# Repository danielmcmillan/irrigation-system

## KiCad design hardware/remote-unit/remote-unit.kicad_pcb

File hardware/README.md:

## PCBs

PCBs are designed using KiCad.

"irrigation-controller" contains the KiCad project for the central control board.

"remote-unit" contains the KiCad project for the remote solenoid control board.

### Libraries

Some project-specific symbols and footprints are saved in the lib dir.

This external symbol and footprint is used with name "TPS54331DR": https://octopart.com/tps54331dr-texas+instruments-12190905

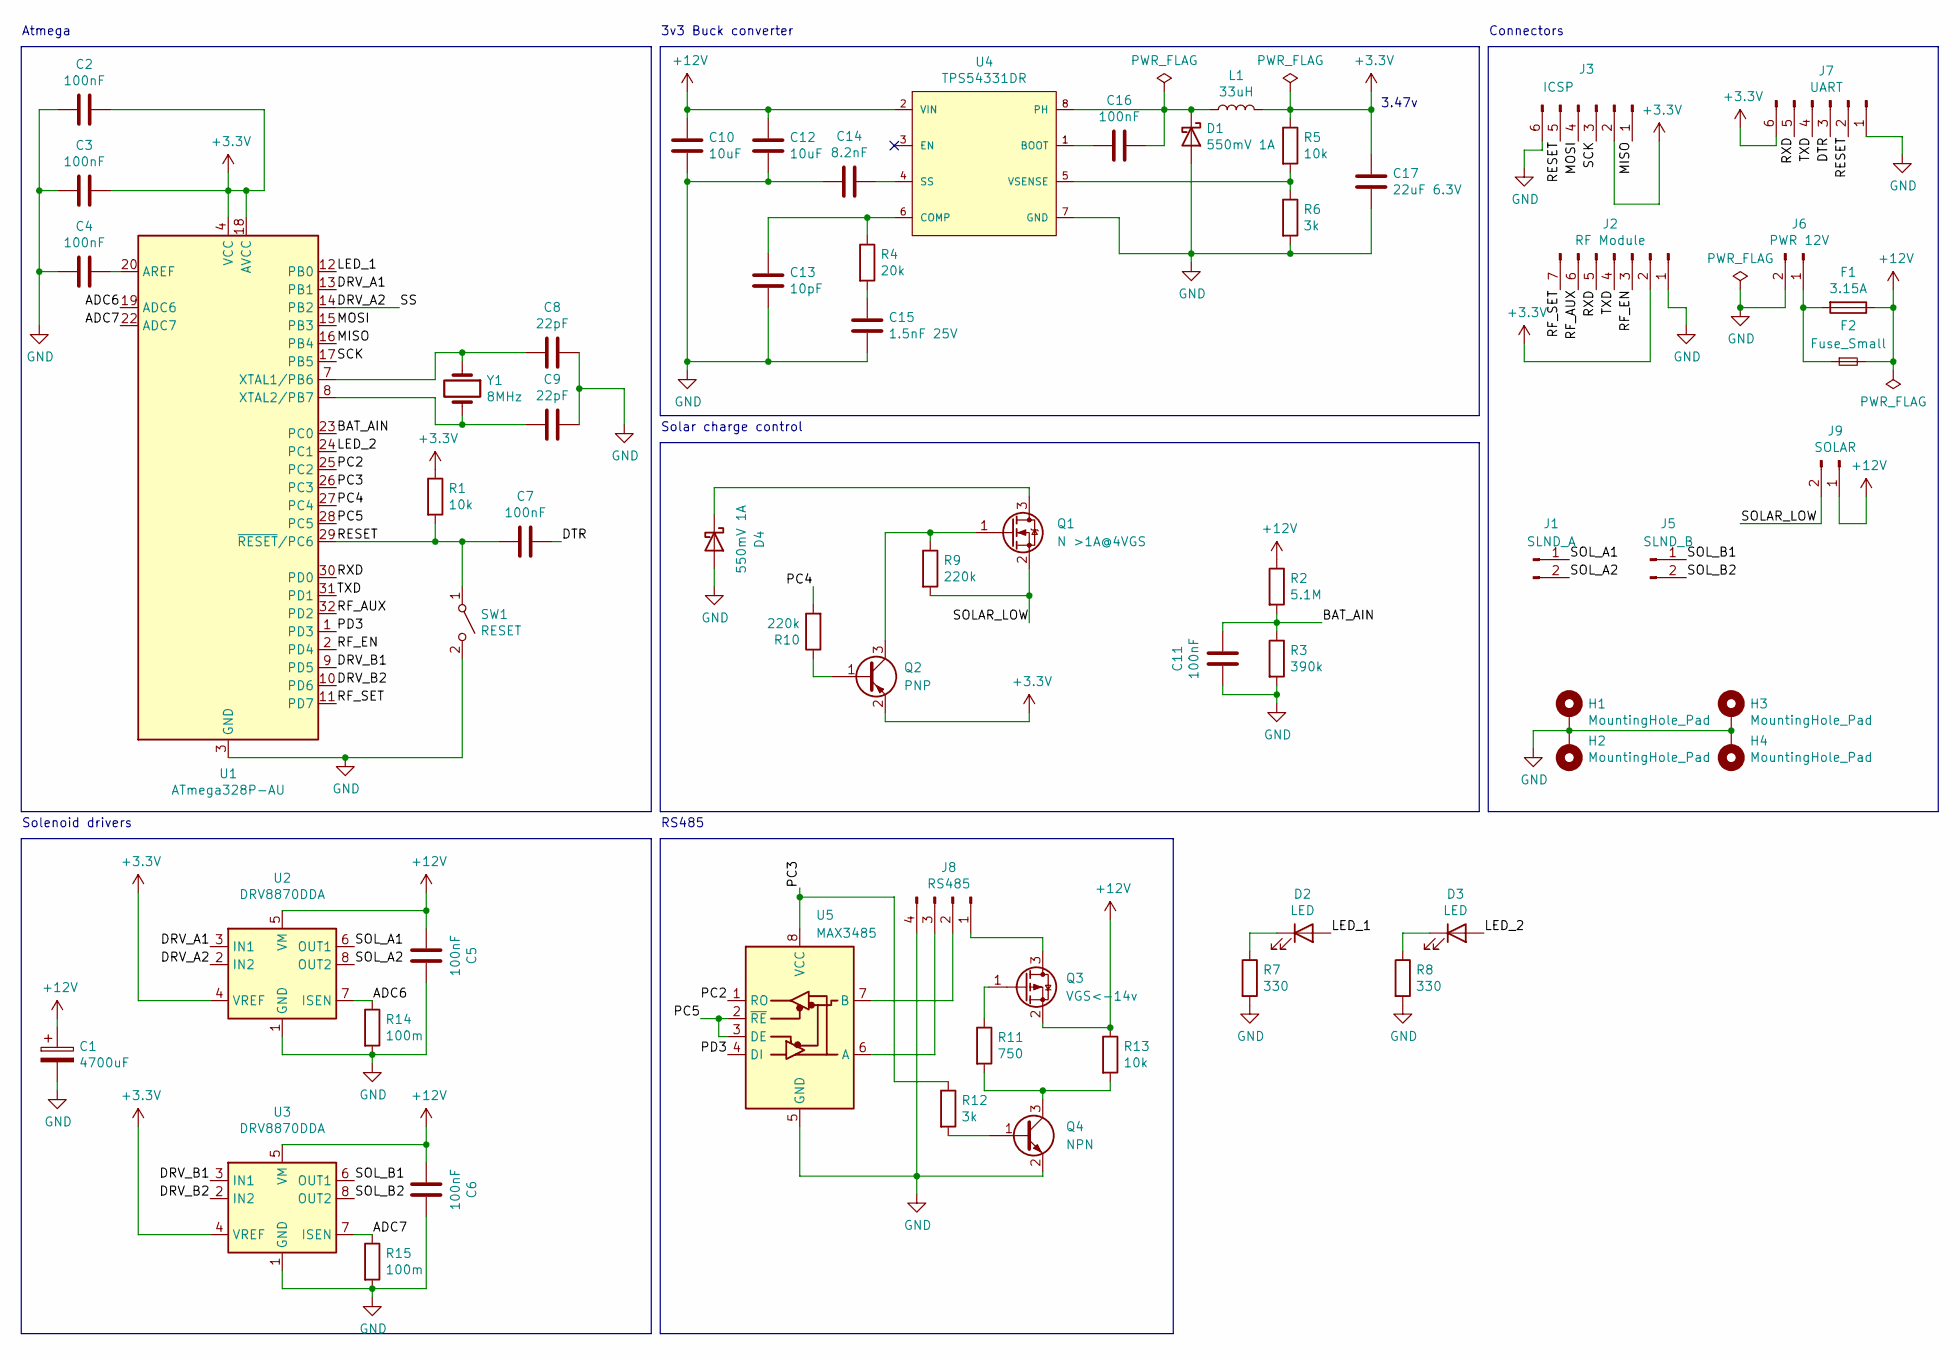
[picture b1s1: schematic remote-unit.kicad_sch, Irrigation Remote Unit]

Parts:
C1: 4700uF; CP_Radial_D16.0mm_P7.50mm
C2, C3, C4, C5, C6, C7, C11, C16: 100nF; C_0603_1608Metric; JLCPCB Part C14663
C8, C9: 22pF; C_0402_1005Metric; JLCPCB Part C1555
C10, C12: 10uF; C_1206_3216Metric; JLCPCB Part C13585
C13: 10pF; C_0603_1608Metric; JLCPCB Part C1634
C14: 8.2nF; C_0603_1608Metric; JLCPCB Part C1322360
C15: 1.5nF 25V; C_0603_1608Metric; JLCPCB Part C1595
C17: 22uF 6.3V; C_0603_1608Metric; JLCPCB Part C59461
D1, D4: 550mV 1A; D_SMA; JLCPCB Part C2480
D2, D3: LED; LED_0603_1608Metric; JLCPCB Part C2286
F1: 3.15A; L_Radial_D8.7mm_P5.00mm_Fastron_07HCP
F2: Fuse_Small; Fuse_0603_1608Metric; JLCPCB Part C163117
H1, H2, H3, H4: MountingHole_Pad; MountingHole_3mm_Pad
J1: SLND_A; JST_XH_B2B-XH-A_1x02_P2.50mm_Vertical
J2: RF Module; YL_800T
J3: ICSP; PinHeader_2x03_P2.54mm_Vertical
J5: SLND_B; JST_XH_B2B-XH-A_1x02_P2.50mm_Vertical
J6: PWR 12V; JST_XH_B2B-XH-A_1x02_P2.50mm_Vertical
J7: UART; PinHeader_2x03_P2.54mm_Vertical
J8: RS485; JST_XH_B4B-XH-A_1x04_P2.50mm_Vertical
J9: SOLAR; JST_XH_B2B-XH-A_1x02_P2.50mm_Vertical
L1: 33uH; L_8x8mm_H4mm; JLCPCB Part C497847
Q1: N >1A@4VGS; SOT-23; JLCPCB Part C20917
Q2: PNP; SOT-23; JLCPCB Part C8542
Q3: VGS<-14v; SOT-23; JLCPCB Part C8492
Q4: NPN; SOT-23; JLCPCB Part C2150
R1, R5, R13: 10k; R_0402_1005Metric; JLCPCB Part C25744
R2: 5.1M; R_0603_1608Metric; JLCPCB Part C13320
R3: 390k; R_0603_1608Metric; JLCPCB Part C23150
R4: 20k; R_0402_1005Metric; JLCPCB Part C25765
R6, R12: 3k; R_0603_1608Metric; JLCPCB Part C4211
R7, R8: 330; R_0402_1005Metric; JLCPCB Part C25104
R9, R10: 220k; R_0603_1608Metric; JLCPCB Part C22961
R11: 750; R_0603_1608Metric; JLCPCB Part C23241
R14, R15: 100m; R_2512_6332Metric; JLCPCB Part C419755
SW1: RESET; SW_SPST_THT_5.0mm
U1: ATmega328P-AU; TQFP-32_7x7mm_P0.8mm; JLCPCB Part C14877
U2, U3: DRV8870DDA; Texas_HTSOP-8-1EP_3.9x4.9mm_P1.27mm_EP2.95x4.9mm_Mask2.4x3.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; JLCPCB Part C86590
U4: TPS54331DR; Texas_Instruments-TPS54331DR-Level_A; JLCPCB Part C9865
U5: MAX3485; MSOP-8_3x3mm_P0.65mm; JLCPCB Part C5310819
Y1: 8MHz; Crystal_SMD_5032-2Pin_5.0x3.2mm; JLCPCB Part C115962

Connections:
+3.3V: C2.1, C3.1, C17.1, J2.2, J3.2, J7.6, L1.2, Q2.2 (E), R1.1, R5.1, U1.4 (VCC), U1.6 (VCC), U1.18 (AVCC), U2.4 (VREF), U3.4 (VREF)
+12V: C1.1, C5.2, C6.2, C10.1, C12.1, F1.1, F2.2, J9.1, Q3.2 (S), R2.1, R13.1, U2.5 (VM), U3.5 (VM), U4.2 (VIN)
/ADC6: R14.1, U1.19 (ADC6), U2.7 (ISEN)
/ADC7: R15.1, U1.22 (ADC7), U3.7 (ISEN)
/BAT_AIN: C11.1, R2.2, R3.1, U1.23 (PC0)
/DRV_A1: U1.13 (PB1), U2.3 (IN1)
/DRV_A2: U1.14 (PB2), U2.2 (IN2)
/DRV_B1: U1.9 (PD5), U3.3 (IN1)
/DRV_B2: U1.10 (PD6), U3.2 (IN2)
/DTR: C7.1, J7.3
/LED_1: D2.2 (A), U1.12 (PB0)
/LED_2: D3.2 (A), U1.24 (PC1)
/MISO: J3.1, U1.16 (PB4)
/MOSI: J3.4, U1.15 (PB3)
/PC2: U1.25 (PC2), U5.1 (RO)
/PC3: R12.1, U1.26 (PC3), U5.8 (VCC)
/PC4: R10.2, U1.27 (PC4)
/PC5: U1.28 (PC5), U5.2 (~RE), U5.3 (DE)
/PD3: U1.1 (PD3), U5.4 (DI)
/RESET: C7.2, J3.5, J7.2, R1.2, SW1.1 (A), U1.29 (~RESET/PC6)
/RF_AUX: J2.6, U1.32 (PD2)
/RF_EN: J2.3, U1.2 (PD4)
/RF_SET: J2.7, U1.11 (PD7)
/RXD: J2.5, J7.5, U1.30 (PD0)
/SCK: J3.3, U1.17 (PB5)
/SOLAR_LOW: J9.2, Q1.2 (S), R9.2
/SOL_A1: J1.1, U2.6 (OUT1)
/SOL_A2: J1.2, U2.8 (OUT2)
/SOL_B1: J5.1, U3.6 (OUT1)
/SOL_B2: J5.2, U3.8 (OUT2)
/TXD: J2.4, J7.4, U1.31 (PD1)
GND: C1.2, C2.2, C3.2, C4.2, C5.1, C6.1, C8.1, C9.1, C10.2, C11.2, C12.2, C13.2, C14.2, C15.2, C17.2, D1.2 (A), D4.2 (A), H1.1, H2.1, H3.1, H4.1, J2.1, J3.6, J6.2, J7.1, J8.4, Q4.2 (E), R3.2, R6.2, R7.2, R8.2, R14.2, R15.2, SW1.2 (B), U1.3 (GND), U1.5 (GND), U1.21 (GND), U2.1 (GND), U2.9 (GND), U3.1 (GND), U3.9 (GND), U4.7 (GND), U5.5 (GND)
unnamed: C15.1, R4.2
unnamed: C16.1, D1.1 (K), L1.1, U4.8 (PH)
unnamed: D2.1 (K), R7.1
unnamed: D3.1 (K), R8.1
unnamed: D4.1 (K), Q1.3 (D)
unnamed: F1.2, F2.1, J6.1
unnamed: J8.1, Q3.3 (D)
unnamed: J8.2, U5.7 (B)
unnamed: J8.3, U5.6 (A)
unnamed: Q1.1 (G), Q2.3 (C), R9.1
unnamed: Q2.1 (B), R10.1
unnamed: Q3.1 (G), R11.1
unnamed: Q4.1 (B), R12.2
unnamed: Q4.3 (C), R11.2, R13.2
unnamed: C4.1, U1.20 (AREF)
unnamed: C8.2, U1.7 (XTAL1/PB6), Y1.1
unnamed: C9.2, U1.8 (XTAL2/PB7), Y1.2
unnamed: C16.2, U4.1 (BOOT)
unnamed: C13.1, R4.1, U4.6 (COMP)
unnamed: C14.1, U4.4 (SS)
unnamed: R5.2, R6.1, U4.5 (VSENSE)

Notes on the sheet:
Atmega
3v3 Buck converter
Solenoid drivers
Solar charge control
RS485
3.47v
Connectors

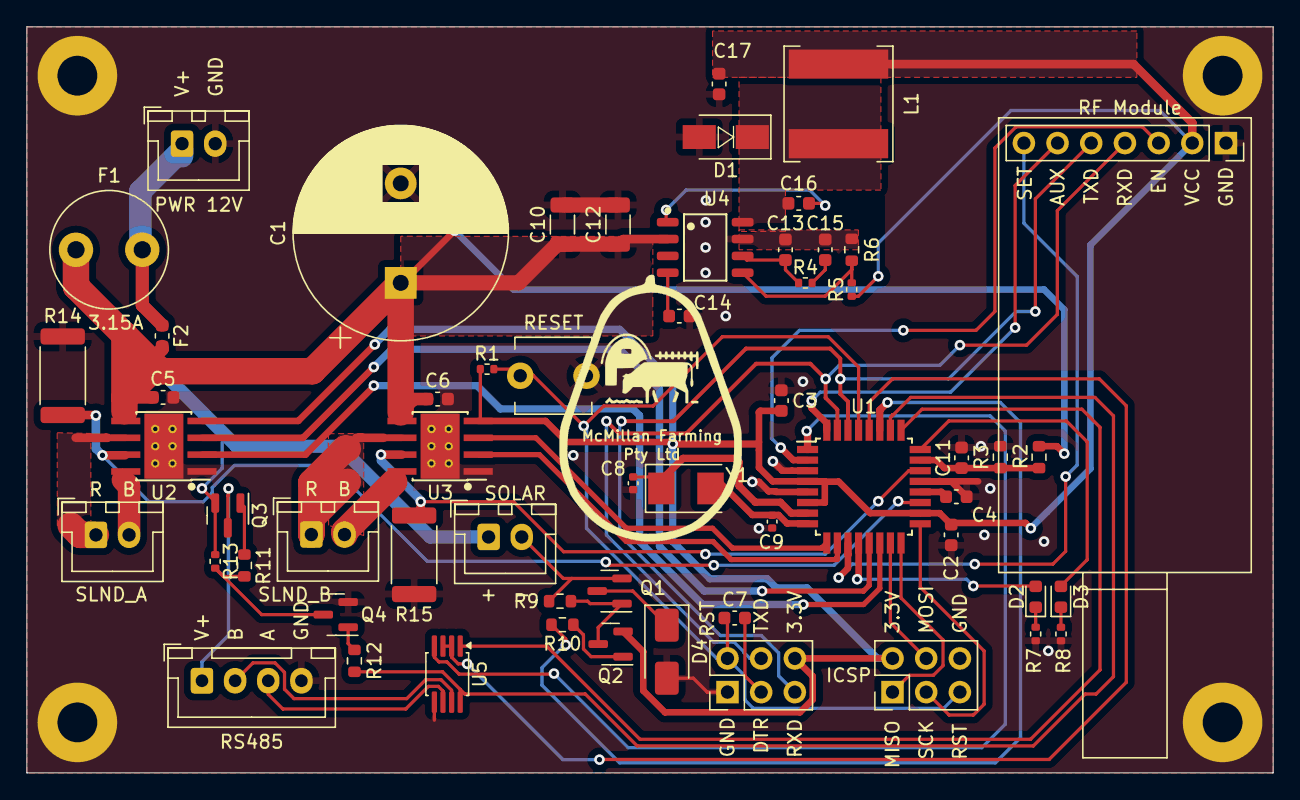
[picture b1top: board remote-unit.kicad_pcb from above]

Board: 2 copper layers, 94.0 x 56.3 mm, 62 parts (0 on the bottom side), 53 nets.

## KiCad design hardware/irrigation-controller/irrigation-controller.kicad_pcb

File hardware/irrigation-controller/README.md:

## Libraries

This symbol and footprint is used with name "TPS54331DR":

https://octopart.com/tps54331dr-texas+instruments-12190905

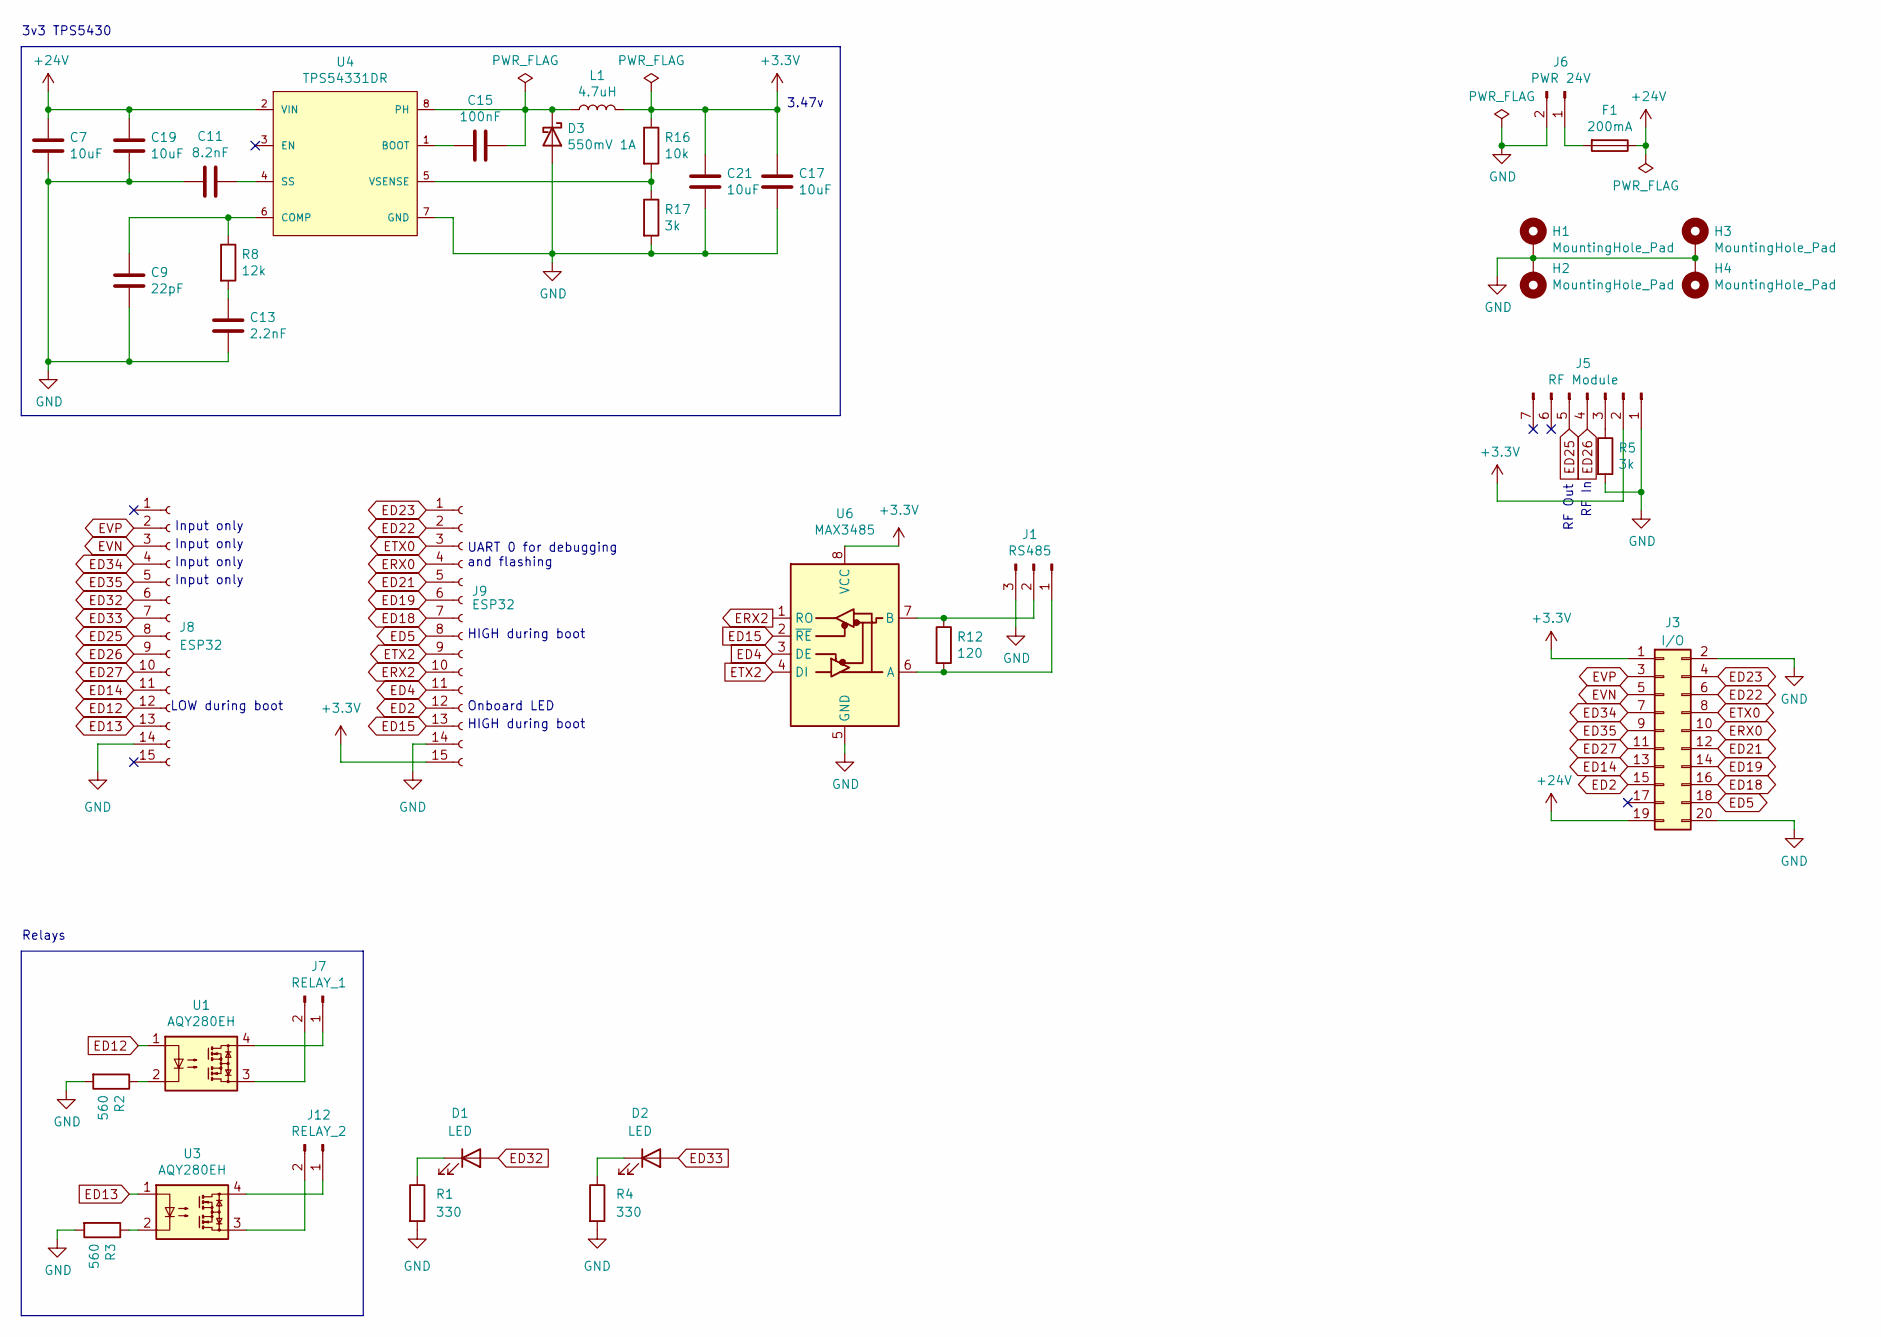
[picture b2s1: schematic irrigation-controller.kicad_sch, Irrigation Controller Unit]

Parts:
C7, C17, C19, C21: 10uF; C_1206_3216Metric; JLCPCB Part C13585
C9: 22pF; C_0603_1608Metric; JLCPCB Part C1653
C11: 8.2nF; C_0603_1608Metric; JLCPCB Part C1322360
C13: 2.2nF; C_0603_1608Metric; JLCPCB Part C1604
C15: 100nF; C_0603_1608Metric; JLCPCB Part C14663
D1, D2: LED; LED_0603_1608Metric; JLCPCB Part C2286
D3: 550mV 1A; D_SMA; JLCPCB Part C2480
F1: 200mA; L_Radial_D8.7mm_P5.00mm_Fastron_07HCP
H1, H2, H3, H4: MountingHole_Pad; MountingHole_3mm_Pad
J1: RS485; JST_XH_B3B-XH-A_1x03_P2.50mm_Vertical
J3: I/O; PinHeader_2x10_P2.54mm_Vertical
J5: RF Module; YL_800T
J6: PWR 24V; JST_XH_B2B-XH-A_1x02_P2.50mm_Vertical
J7: RELAY_1; JST_XH_B2B-XH-A_1x02_P2.50mm_Vertical
J8, J9: ESP32; PinSocket_1x15_P2.54mm_Vertical
J12: RELAY_2; JST_XH_B2B-XH-A_1x02_P2.50mm_Vertical
L1: 4.7uH; L_Changjiang_FNR4020S; JLCPCB Part C167828
R1, R4: 330; R_0402_1005Metric; JLCPCB Part C25104
R2, R3: 560; R_0603_1608Metric; JLCPCB Part C23204
R5, R17: 3k; R_0603_1608Metric; JLCPCB Part C4211
R8: 12k; R_0603_1608Metric; JLCPCB Part C22790
R12: 120; R_0603_1608Metric; JLCPCB Part C22787
R16: 10k; R_0402_1005Metric; JLCPCB Part C25744
U1, U3: AQY280EH; DIP-4_W7.62mm
U4: TPS54331DR; Texas_Instruments-TPS54331DR-Level_A; JLCPCB Part C9865
U6: MAX3485; DIP-8_W7.62mm

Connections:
+3.3V: C17.1, C21.1, J3.1, J5.2, J9.15, L1.2, R16.1, U6.8 (VCC)
+24V: C7.1, C19.1, F1.1, J3.19, U4.2 (VIN)
ED2: J3.15, J9.12
ED4: J9.11, U6.3 (DE)
ED5: J3.18, J9.8
ED12: J8.12, U1.1
ED13: J8.13, U3.1
ED14: J3.13, J8.11
ED15: J9.13, U6.2 (~RE)
ED18: J3.16, J9.7
ED19: J3.14, J9.6
ED21: J3.12, J9.5
ED22: J3.6, J9.2
ED23: J3.4, J9.1
ED25: J5.5, J8.8
ED26: J5.4, J8.9
ED27: J3.11, J8.10
ED32: D1.2 (A), J8.6
ED33: D2.2 (A), J8.7
ED34: J3.7, J8.4
ED35: J3.9, J8.5
ERX0: J3.10, J9.4
ERX2: J9.10, U6.1 (RO)
ETX0: J3.8, J9.3
ETX2: J9.9, U6.4 (DI)
EVN: J3.5, J8.3
EVP: J3.3, J8.2
GND: C7.2, C9.2, C11.2, C13.2, C17.2, C19.2, C21.2, D3.2 (A), H1.1, H2.1, H3.1, H4.1, J1.3, J3.2, J3.20, J5.1, J6.2, J8.14, J9.14, R1.2, R2.2, R3.2, R4.2, R5.2, R17.2, U4.7 (GND), U6.5 (GND)
unnamed: C13.1, R8.2
unnamed: D1.1 (K), R1.1
unnamed: D2.1 (K), R4.1
unnamed: C15.1, D3.1 (K), L1.1, U4.8 (PH)
unnamed: J1.1, R12.2, U6.6 (A)
unnamed: J1.2, R12.1, U6.7 (B)
unnamed: J5.3, R5.1
unnamed: F1.2, J6.1
unnamed: J7.1, U1.4
unnamed: J7.2, U1.3
unnamed: J12.1, U3.4
unnamed: J12.2, U3.3
unnamed: R2.1, U1.2
unnamed: R3.1, U3.2
unnamed: C15.2, U4.1 (BOOT)
unnamed: C9.1, R8.1, U4.6 (COMP)
unnamed: C11.1, U4.4 (SS)
unnamed: R16.2, R17.1, U4.5 (VSENSE)

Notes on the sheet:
RF Out
RF In
Input only
Onboard LED
HIGH during boot
LOW during boot
UART 0 for debugging and flashing
3.47v
Relays
3v3 TPS5430

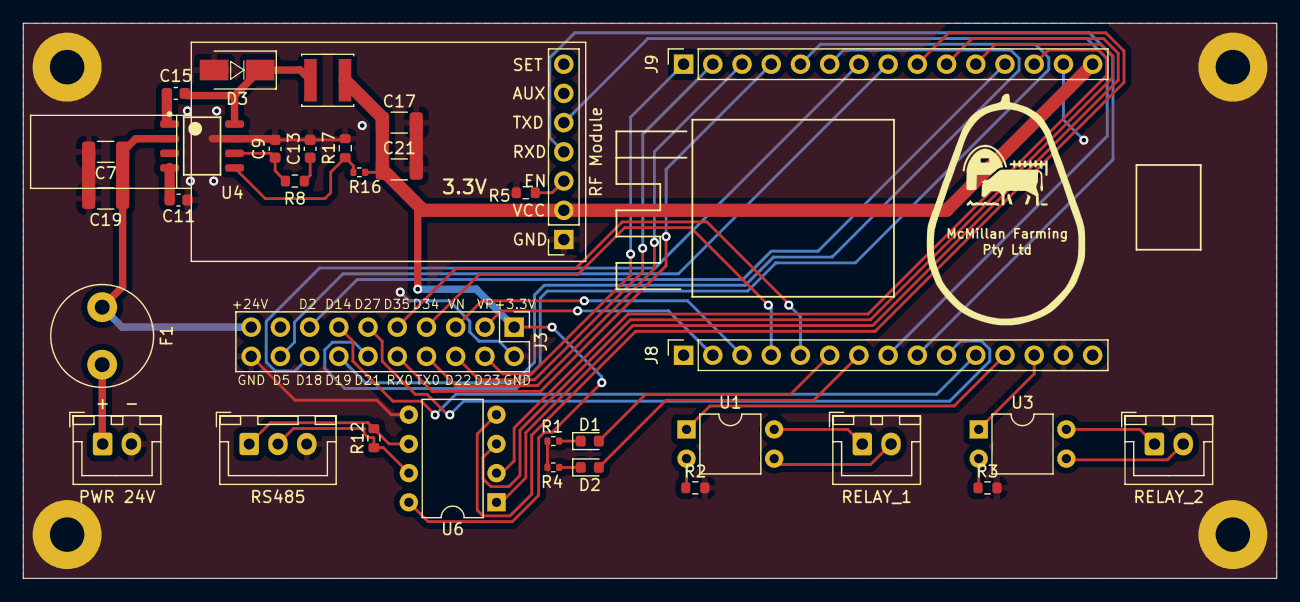
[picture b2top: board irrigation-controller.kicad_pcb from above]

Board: 2 copper layers, 109.0 x 48.3 mm, 38 parts (0 on the bottom side), 46 nets.

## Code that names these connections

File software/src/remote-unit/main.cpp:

#include <Arduino.h>
#include <avr/sleep.h>
#include "yl-800t.h"
#include "serial-interface.h"
#include "config.h"
#include "rf-module.h"
#include "solenoids.h"
#include "battery.h"
#include "faults.h"
#include "sensor.h"
#include "settings.h"

#define SERIAL_BEGIN Serial.begin(9600, SERIAL_8N1)

// Pins
#define RF_EN 4
#define LED_1 8
#define LED_2 A1
#define RF_INTERRUPT_PIN 2
#define RF_INTERRUPT_NUMBER 0

// Solenoid driver pins
#define DRV_A1 9
#define DRV_A2 10
#define DRV_B1 5
#define DRV_B2 6

// Solenoid current sense pins
#define SOL_A_ADC 6
#define SOL_B_ADC 7

// Pulled low to enable solar charge
#define DISABLE_CHARGE A4

// RS485 sensor pins
#define RS_485_RX_PIN A2    // PC2
#define RS_485_TX_PIN 3     // PD3
#define RS_485_RE_DE_PIN A5 // SCL
#define RS485_ENABLE_PIN A3 // PC3

unsigned long lastSuccessfulCommunicationCounts = 0;
volatile bool dataPending = false;
// Approximation of time elapsed, multiples of 8 seconds
volatile unsigned long counts = 0;

RemoteUnitConfig config;
SolenoidDefinition solenoidDefinitions[] = {
    {DRV_A1, DRV_A2, SOL_A_ADC},
    {DRV_B1, DRV_B2, SOL_B_ADC}};
RemoteUnitRfModule rfModule(NODE_ID, config, RF_EN);
Solenoids solenoids(config, solenoidDefinitions);
RemoteUnitBattery battery(config, 0, DISABLE_CHARGE);
RemoteUnitFaults faults;
RemoteUnitSensor sensor(config, RS_485_RX_PIN, RS_485_TX_PIN, RS_485_RE_DE_PIN, RS485_ENABLE_PIN);
RemoteUnitCommandHandler commandHandler(config, rfModule, solenoids, battery, faults, sensor, counts);
RemoteUnitSerialInterface remoteUnitSerial(NODE_ID, commandHandler);

void handleRfModuleInterrupt()
{
    dataPending = true;

    // We need to wake up the RF module as quickly as possible.
    // Warning - maybe concurrency issue if writing something different in loop.
    rfModule.wake();
}

// Watchdog timer interrupt handler
ISR(WDT_vect)
{
    ++counts;
}

void enableTimerInterrupt()
{
    // Watchdog timer interrupt
    // Clear the WD reset flag.
    MCUSR &= ~(1 << WDRF);

    // Set WD change enable and WD system reset enable
    WDTCSR |= (1 << WDCE) | (1 << WDE);

    // Configure the WD prescaler, unset WDE
    WDTCSR = 1 << WDP0 | 1 << WDP3; // 8 seconds

    // Enable the WD interrupt
    WDTCSR |= 1 << WDIE;
}

void enableRfModuleInterrupt()
{
    // Enable pull-up on interrupt pin
    pinMode(RF_INTERRUPT_PIN, INPUT_PULLUP);
    attachInterrupt(RF_INTERRUPT_NUMBER, handleRfModuleInterrupt, FALLING);
}

void sleep()
{
    // Turns off modules and puts the processor to sleep until RF is received
    // Based on tips from https://www.gammon.com.au/forum/?id=11497
    rfModule.sleep();
    // Put motor drivers to sleep
    solenoids.sleep();

    // Disable ADC - this caused problems
    // ADCSRA = 0;

    set_sleep_mode(SLEEP_MODE_PWR_DOWN);
    sleep_enable();

    // turn off brown-out enable in software
    noInterrupts();
    // BODS must be set to one and BODSE must be set to zero within four clock cycles
    MCUCR = bit(BODS) | bit(BODSE);
    // The BODS bit is automatically cleared after three clock cycles
    MCUCR = bit(BODS);
    // We are guaranteed that the sleep_cpu call will be done
    // as the processor executes the next instruction after
    // interrupts are turned on.
    interrupts(); // one cycle

    sleep_cpu();
    // Continues from here after wake
    sleep_disable();
}

void setup()
{
    SERIAL_BEGIN;
    pinMode(LED_1, OUTPUT);
    pinMode(LED_2, OUTPUT);
    // Startup LED flashing sequence
    for (int i = 0; i < 4; ++i)
    {
        digitalWrite(LED_1, HIGH);
        digitalWrite(LED_2, LOW);
        delay(150);
        digitalWrite(LED_1, LOW);
        digitalWrite(LED_2, HIGH);
        delay(150);
    }
    digitalWrite(LED_2, LOW);

    if (config.load())
    {
        faults.setFault(RemoteUnitFault::ConfigReadFailed);
    }
    rfModule.setup();
    solenoids.setup();
    battery.setup();
    sensor.setup();
    if (rfModule.applyConfig())
    {
        faults.setFault(RemoteUnitFault::ConfigureRfModuleFailed);
    }

    noInterrupts();
    enableRfModuleInterrupt();
    enableTimerInterrupt();
    interrupts();
}

void loop()
{
    bool handleSerialData = dataPending;
    digitalWrite(LED_1, HIGH);
    if (handleSerialData)
    {
        rfModule.wake();
        SERIAL_BEGIN;
    }
    else
    {
        // Only do battery and sensor updates when not handling RF data
        if (battery.update(counts))
        {
            faults.setFault(RemoteUnitFault::BatteryVoltageError);
        }
        sensor.update(counts);
    }

    if (handleSerialData)
    {
        digitalWrite(LED_2, HIGH);
        // Read a packet from Serial and perform any encoded commands.
        RemoteUnitSerialInterface::Result result = remoteUnitSerial.receivePacket(5000);
        digitalWrite(LED_2, LOW);

        // Flash to show error
        if (result != RemoteUnitSerialInterface::Result::success && result != RemoteUnitSerialInterface::Result::noData)
        {
            delay(300);
            for (int i = 0; i < (uint8_t)result; ++i)
            {
                digitalWrite(LED_2, HIGH);
                delay(300);
                digitalWrite(LED_2, LOW);
                delay(300);
            }
        }
        if (result == RemoteUnitSerialInterface::Result::success)
        {
            lastSuccessfulCommunicationCounts = counts;
        }
    }

    if (counts - lastSuccessfulCommunicationCounts > ((unsigned long)(config.getCommunicationTimeout())))
    {
        // No successful communication received for the configured timeout
        // Revert non-persisted config
        if (config.getIsChanged())
        {
            SERIAL_BEGIN;
            if (config.load())
            {
                faults.setFault(RemoteUnitFault::ConfigReadFailed);
            }
            if (rfModule.applyConfig())
            {
                faults.setFault(RemoteUnitFault::ConfigureRfModuleFailed);
            }
        }
        // Ensure valves are shut off
        if ((solenoids.getState() & ~SOLENOID_FORCE_FLAG) != 0)
        {
            faults.setFault(RemoteUnitFault::SolenoidTimeoutOccurred);
            solenoids.setState(0);
        }
    }
    if (handleSerialData)
    {
        // Allow some extra time for RF data to be sent before sleep
        delay(34);
        dataPending = Serial.available() > 0;
    }
    if (!dataPending)
    {
        Serial.end();
        digitalWrite(LED_1, LOW);
        sleep();
    }
}

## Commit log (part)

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2021-09-07 Add more controller board connectors
2021-09-08 Add controller relay 4
2021-09-08 Add i2c_2
2021-09-08 Add controller PWR input
2021-09-09 Update board settings
2021-09-09 Fix relay symbol pins
2021-09-09 Initial controller pcb footprint import
2021-09-10 Add SW2 and FLOW header
2021-09-12 Controller pcb layout mostly complete
2021-09-12 Route all controller board nets
2021-09-12 Controller pcb silkscreen fixup
2021-09-12 Increase clearance for controller board
2021-09-12 Add avocado image to controller board
2021-09-12 Fix missing smd flags
2021-09-14 Controller board cosmetic changes
2021-09-14 Add jlcpcb steps
2021-09-18 Add dot marker on motor drivers
2021-10-17 Update inductor footprint on remote unit
2021-10-18 Add boost converter for solar panel
2021-10-29 Fix remote unit buck converter
    Compensation capacitor value was wrong.
    Move output capacitor closer.
2021-11-13 Set up PlatformIO
2021-11-13 Add CRC implementation
2021-11-16 Prototype I2C communication with crc
2021-12-30 More i2c communication testing
2021-12-31 Add library for controlling motor driver over Modbus
2022-01-01 Add controller interface and vacon controller
2022-01-02 Controller registration
2022-01-05 Track availability of vacon controller
2022-01-08 Initial http server
2022-03-20 Add yl-800t submodule
2022-04-25 Initial functions for building remote unit data packets
2022-04-26 Initial CLI for testing remote unit
2022-04-29 Remote unit interface with stub commands
2022-04-29 Add class for remote unit config
2022-04-29 Add class for solenoid control
2022-04-29 Handle remote unit solenoid commands
2022-04-29 Handle remote unit battery commands
2022-04-29 Handle remote unit config commands
2022-04-29 Apply config to remote unit rf module
2022-04-29 Apply configured remote unit solenoid timeout
2022-04-29 Handle remote unit fault codes
2022-04-29 Persist remote unit config in EEPROM
2022-04-29 Fix remote unit cli serial timeout
2022-04-29 Support multiple commands in remote unit cli
2022-04-29 Support forcing remote unit solenoid activation
2022-04-30 Remote unit update LED indicators
2022-04-30 Remote unit periodic wake
2022-04-30 Improve reliability of remote unit communication
2022-04-30 Remote unit sleep when maintaining battery and add get timer command
2022-04-30 Handle packet build error in remote unit cli
2022-05-01 Apply remote unit rf module config after config timeout
2022-05-01 Mathematical round of remote unit voltage reading
2022-05-01 Fix apply RF config command not sending response
2022-05-01 Add remote unit software revision number
2022-05-01 Fix remote unit fail to configure RF module on powerup
2022-07-04 Remove port settings
2022-08-06 Add controller definition provider
2022-09-25 Add control processor i2c packet handling
2022-11-19 Notes moved to wiki
2022-11-20 Update env config
2022-12-30 Add basic Vacon Modbus simulator
2022-12-31 Add response size to I2C responses
2022-12-31 Control processor reorganisation
2022-12-31 Add controller and definition builder class
2022-12-31 Add additional Vacon parameter support
2023-01-02 Add control processor event history
2023-01-02 Support iterating property ids in controller definition
2023-01-02 Raise events for changes to Vacon data
2023-01-02 Raise events for Vacon communication errors
2023-01-03 Fix error when missing event handler
2023-01-03 Fix incorrect values read from Modbus
2023-01-03 Fix narrowing conversion warning
2023-01-03 Cut down TwoWire library to save memory
2023-01-04 Cut down libmodbus library to save memory
2023-01-04 Move libraries
2023-01-04 Fix rs485 begin not called
2023-01-04 Test HTTP API for events
2023-01-04 Replace event timestamp with sequential id
2023-01-04 Improve event HTTP api
2023-02-18 Web init
2023-02-18 Remove control processor packet getResponseSize
    Because packets can be variable size, size doesn't need to be known
2023-02-19 Add error threshold before Vacon 100 is considered unavailable
2023-02-24 Fix warning
2023-02-25 Add remote unit definition and config
2023-02-26 Add periodic read from remote units
2023-02-26 Improve remote unit error handling
2023-03-10 Remote unit update scheduling and apply changes
2023-03-10 Timing adjustment for remote unit
2023-03-11 Vacon100 update scheduling
2023-03-12 Implement control processor configuration
2023-03-12 Add wifi manager
2023-03-16 Mqtt client
2023-03-18 Topic subscription
2023-03-18 Parse incoming message topic
2023-03-18 Handle config from mqtt
2023-03-18 Use vite for building ui
2023-03-19 Add net host error handler
2023-03-19 Handle errors
2023-03-19 Decouple events from mqtt client
2023-03-19 Provide more metadata in controller definitions
2023-03-19 Implement property state retrieval
2023-03-19 Implement config retrieval
2023-03-19 Persist config
2023-03-19 Fix remote unit property names
2023-03-20 ControllerManager updateControllers
2023-03-20 Support controller specific commands
2023-03-20 Support custom vacon and remote unit access
2023-03-26 Fix web ui build
2023-03-26 Add clear log button
2023-03-26 AWS config from env
2023-03-26 Fix mobile scrolling
2023-03-29 Improve vacon simulator
2023-03-29 Stringify controller error codes
2023-03-29 Fix modbus write response handling
2023-03-30 Refresh properties in ui when config resets
2023-04-01 Fix config page
2023-04-01 Config UI stepper fields
2023-04-02 Support controller command on mqtt
2023-04-02 Add UI for Vacon read/write
2023-04-05 Update web ui config
2023-04-05 Remote unit return fault code on clear
2023-04-05 UI mqtt device id configured in environment
2023-04-05 Update property names
2023-04-07 Fix subscribing to all devices
2023-04-07 Fix feedback pressure unit
2023-04-07 Add i2c get state command
2023-06-24 Update at most one remote unit each interval
2023-06-24 Combine control processor with net host
2023-06-24 Support control-processor OTA updates
2023-06-24 Don't block startup on Vacon ID map update
2023-06-24 Add UI for some remote unit commands
2023-06-26 Fix controller event history buffer overflow
2023-06-26 Add initial cloud event handler
2023-06-26 Use text area for config UI
2023-07-01 Fix other controller event history buffer overflow
2023-07-01 Translate remote unit faults to text in UI
2023-07-02 Update remote unit default timeout to 840s
2023-07-02 Better handling of connection status in ui
2023-07-04 Refactor controller event history
2023-07-22 Store device state in dynamodb
2023-07-22 Store historical property values
2023-07-30 Add connected and config to device state
2023-08-13 Add initial v2 app with login and ws API
2023-08-20 Add initial push notifications support
2023-08-26 Add web push keys to environment
2023-08-27 Add react-use-websocket
2023-09-03 Store WebSocket client connections
2023-10-01 Add ws all state query + wip controller definitions
2023-10-02 Add remote unit RS485 moisture sensor support
2023-10-02 Read sensor value from configured remote units
2023-10-02 Config editor fix
2023-10-03 Fix iteration of remote unit properties
2023-10-28 Irrigation controller Kicad 7 schematic
2023-11-20 Support configuration of rs485 sensor power-on delay
2023-11-25 Use ESM for AWS web service
2023-11-25 Update for new control processor hardware
2023-11-25 Add RS485 to remote unit schematic
2023-11-25 Update remote unit PCB
2023-11-25 Fix controller Vacon relay pin
2023-11-25 Fix modbus error code getting truncated
2023-12-20 Increase timeout when reading sensor
2023-12-20 Sensor value conversion for old UI
2023-12-21 Add id for controller commands
2023-12-21 Fix crash caused by invalid mqtt topic
2023-12-21 Package updates
2023-12-22 Increase supported remote unit count
2023-12-23 Use MQTT QoS 1 and persistent sessions
2024-01-14 Encode sensor reading errors in result
2024-01-14 Skip RF init when there are no remote units
2024-01-21 Remote unit LED flashing on startup
2024-01-22 Update remote unit controller sensor value handling
2024-01-22 Remote unit automatic scheduling for sensor reading
2024-01-23 gitignore updates
2024-01-23 Store timestamp as BE in DynamoDB key for historical data
2024-01-23 Send remote unit available events even when there is no change
2024-01-23 Publish with QoS 1 to avoid missed events
2024-01-25 Fix sending two started events on first control unit startup
2024-01-26 Renaming for device message types
2024-01-26 Fix push notification error handling
2024-01-26 Add controller definitions to API service
2024-01-27 Use node 20 Lambda runtime
2024-01-27 Support set property websocket message
2024-01-27 Initial v1 ui working with websocket API
    No log, config or tool support
2024-01-31 Support websocket api property history requests
2024-01-31 Update sensor conversion in old ui
2024-02-03 Fix remote unit charge control FET pin mismatch
2024-02-04 Don't write property to store when no update occurred
2024-02-10 Renaming of some websocket events
2024-02-10 Support websocket api config requests
2024-02-10 Support websocket api controller commands
2024-02-11 Add GitHub workflow for ui2
2024-02-11 Fix Cognito refresh
2024-02-11 Fix ui2 build
2024-02-11 Use location.origin for redirectUrl
2024-02-11 Add ui v1 GitHub Workflow
2024-02-11 Add staging URLs as allowed redirect URLs
2024-02-11 Set branch for CloudFlare pages
2024-02-11 npm package updates
2024-02-11 Fix ui1 environment
2024-02-11 Support websocket reconnect after retry fails
2024-02-11 Upgrade react-use-websocket
2024-03-28 Property history
2024-03-30 Fix ui2 controller connected status
2024-03-31 ui2 hardcoded property group ordering
2024-03-31 Improve ui2 login redirect logic
2024-03-31 Add ui2 logout button
2024-04-01 Hide empty mositure sensor value in ui
2024-04-01 Refactor ui remote unit tool
2024-04-01 Add read sensor to remote unit tool
2024-04-01 Add command to get controller received signal strength
2024-04-01 Fix ui property filter
2024-04-01 Add zones to sensor component name
2024-04-01 Fix property list ui not updating
2024-04-01 Support setting ui device id
2024-04-02 Avoid recording unknown/empty property values
2024-04-02 Fix property read error message
2024-04-02 Extend queried property history time period
2024-04-02 Fix ui showing undefined in logs
2024-04-03 Update npm dependencies
2024-04-05 Add fertigation flow rate sensor
2024-08-10 Add staging environment for workflow
2024-08-11 Add device schedule to API
2024-08-11 Fix prop name mismatch
2024-10-26 Initial scheduling ui
2024-10-26 Separate slider for hours and minutes
2024-10-26 Improve schedule entry list ui
2024-11-03 Initial scheduling backend support
2024-11-03 Fix handling of schedule abort
2024-11-03 Provide schedule status to websocket clients
2024-11-03 Send push notification when schedule is aborted
2024-11-03 Abort schedule when device restarts
2024-11-03 Filter web push notifications by device id
2024-11-03 Unique ui app title for different stages
2024-11-03 Better abort handling in schedule list
2024-11-03 Update npm packages
2024-11-03 Use warning alert colour when schedule has pending items
2024-11-03 Shorten push notification titles
2024-11-03 Auto-reload ui when there's an update
2024-11-16 Add blur behind tabs
2024-11-17 Notify instead of abort if less than 3 scheduled properties are failing
2024-11-17 Basic alignment of schedule entry times
2025-11-09 Remote unit Kicad upgrade
2025-11-09 Fix remote unit rs485 sensor power supply circuit
    Replace BJT with mosfet with appropriate source-gate voltage rating
2025-11-09 Update remote unit buck converter
    Update compensation network values.
    Redo layout.
2025-11-09 Add SMT fuse to remote unit
2025-11-09 Use SMT MAX3485 for remote unit
2025-11-11 Add remote unit current sense resistors
2025-11-30 Remote unit reporting low current fault
2025-12-20 Push notification for low solenoid current
2026-04-10 Disable remote unit voltage alerts
2026-04-10 Default schedules to 5 minutes
2026-04-10 aws package updates
2026-04-11 UI for saved schedules
2026-04-11 Schedule list layout changes
2026-04-11 Combine saved schedule buttons
